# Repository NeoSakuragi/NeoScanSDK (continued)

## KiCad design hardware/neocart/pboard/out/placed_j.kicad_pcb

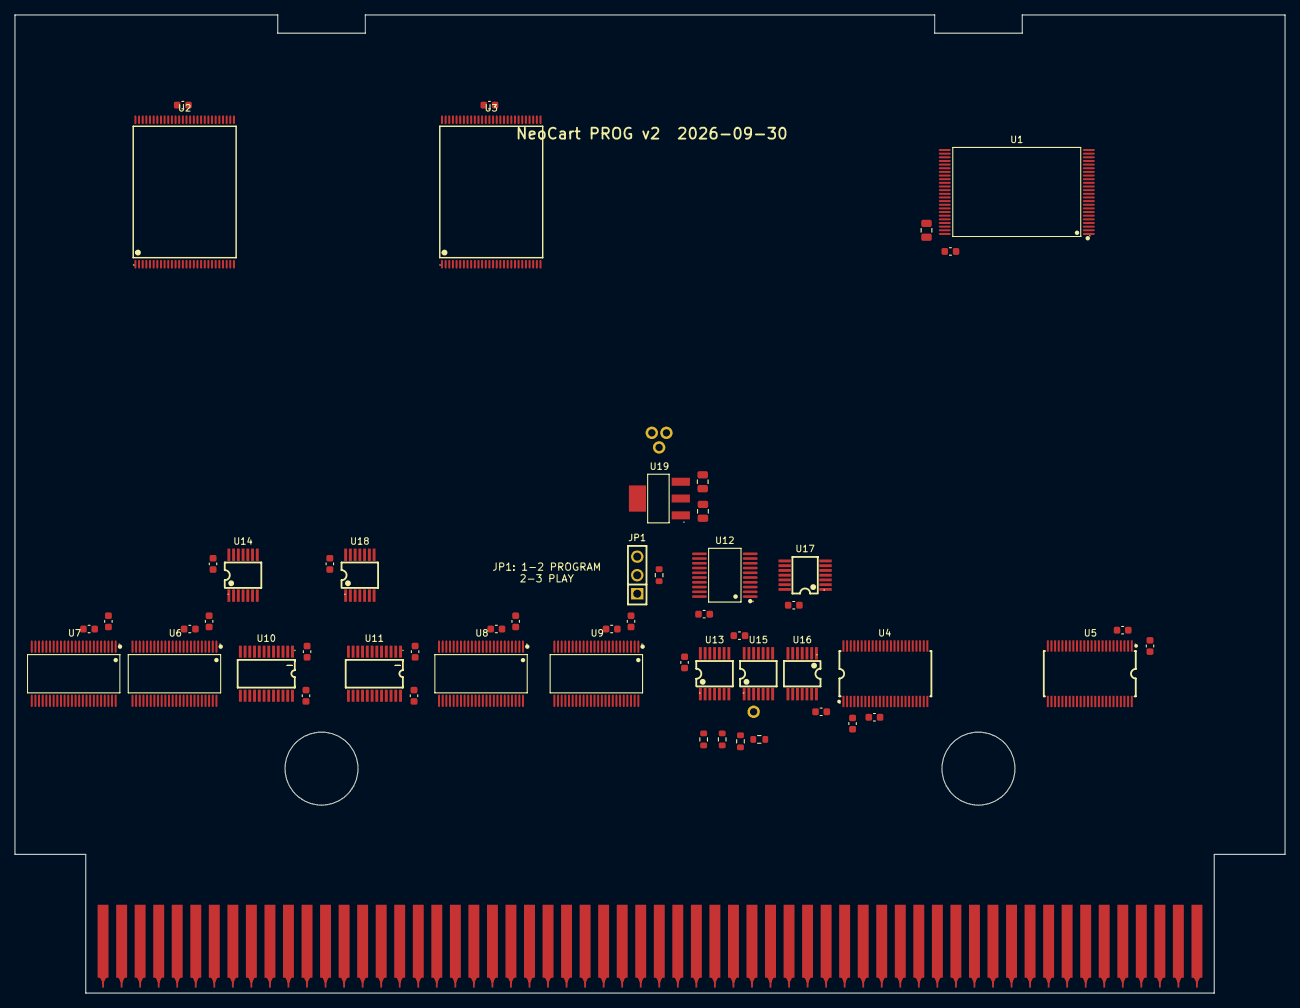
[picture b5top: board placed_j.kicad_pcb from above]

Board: 2 copper layers, 174.0 x 134.0 mm, 60 parts (1 on the bottom side), 202 nets, no tracks yet.

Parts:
C1, C2, C3: 10u; C_0805_2012Metric
C4, C5, C6, C7, C8, C9, C10, C11, C12, C13, C14, C15, C16, C17, C18, C19, C20, C21, C22, C23, C24, C25, C26, C27, C28, C29: 100n; C_0603_1608Metric
J1: NeoGeo MVS Prog B Side Edge; neogeo-mvs-prog-b-side-edge
J2: NeoGeo MVS Prog A Side Edge; neogeo-mvs-prog-a-side-edge
JP1: MODE; HDR-TH_03P-P2.54-V-M
R1, R2, R3, R4, R5: 10k; R_0603_1608Metric
TP1: GND; TP_PTH_1.0
TP2: P3V3; TP_PTH_1.0
TP3: VCC5; TP_PTH_1.0
TP4: nPROG; TP_PTH_1.0
U1: S29GL064N; TSOP-48_L12.0-W18.4-P0.50-LS20.0-BL
U2, U3: S29GL128P; TSOP-56_L18.4-W14.0-P0.50-LS20.0-TL
U4, U5: SN74LVC16245A; TSSOP-48_L12.5-W6.1-P0.50-LS8.1-BL
U6, U7, U8, U9: 74LVC16374A; TSSOP-48_L12.6-W6.2-P0.50-LS8.1-BL
U10, U11: 74LVC8T245; TSSOP-24_L7.8-W4.4-P0.65-LS6.4-BL
U12: SN74AHC273; SSOP-20_L7.5-W5.2-P0.65-LS8.0-BL
U13, U14: SN74LVC08A; TSSOP-14_L5.0-W4.4-P0.65-LS6.4-BL
U15, U16, U17: 74LVC32A; TSSOP-14_L5.0-W4.4-P0.65-LS6.4-BL
U18: SN74LVC04A; TSSOP-14_L5.0-W4.4-P0.65-LS6.4-BL
U19: AMS1117-3.3; SOT-223-3_L6.5-W3.4-P2.30-LS7.0-BR

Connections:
A1: J1.5 (A1), U5.47
A2: J1.6 (A2), U5.46
A3: J1.7 (A3), U5.44
A4: J1.8 (A4), U5.43
A5: J1.9 (A5), U5.41
A6: J1.10 (A6), U5.40
A7: J1.11 (A7), U5.38
A8: J1.12 (A8), U5.37
A9: J1.13 (A9), U5.36
A10: J1.14 (A10), U5.35
A11: J1.15 (A11), U5.33
A12: J1.16 (A12), U5.32
A13: J1.17 (A13), U5.30
A14: J1.18 (A14), U5.29
A15: J1.19 (A15), U5.27
A16: J1.20 (A16), U5.26
A17: J1.21 (A17), U16.12
A18: J1.22 (A18), U17.1
A19: J1.23 (A19), U17.4
BANK0: U12.2, U16.1
BANK1: U12.5, U16.4
BANK2: U12.6, U16.9
D0: J2.5 (D0), U4.23
D1: J2.6 (D1), U4.22
D2: J2.7 (D2), U4.20
D3: J2.8 (D3), U4.19
D4: J2.9 (D4), U4.17
D5: J2.10 (D5), U4.16
D6: J2.11 (D6), U4.14
D7: J2.12 (D7), U4.13
D8: J2.13 (D8), U4.12
D9: J2.14 (D9), U4.11
D10: J2.15 (D10), U4.9
D11: J2.16 (D11), U4.8
D12: J2.17 (D12), U4.6
D13: J2.18 (D13), U4.5
D14: J2.19 (D14), U4.3
D15: J2.20 (D15), U4.2
FA0: U1.25, U5.2
FA1: U1.24, U5.3
FA2: U1.23, U5.5
FA3: U1.22, U5.6
FA4: U1.21, U5.8
FA5: U1.20, U5.9
FA6: U1.19, U5.11
FA7: U1.18, U5.12
FA8: U1.8, U5.13
FA9: U1.7, U5.14
FA10: U1.6, U5.16
FA11: U1.5, U5.17
FA12: U1.4, U5.19
FA13: U1.3, U5.20
FA14: U1.2, U5.22
FA15: U1.1, U5.23
FA16: U1.48, U16.11
FA17: U1.17, U17.3
FA18: U1.16, U17.6
FA19: U1.9, U16.3
FA20: U1.10, U16.6
FA21: U1.13, U16.8
FD0: U1.29, U4.26, U12.3
FD1: U1.31, U4.27, U12.4
FD2: U1.33, U4.29, U12.7
FD3: U1.35, U4.30
FD4: U1.38, U4.32
FD5: U1.40, U4.33
FD6: U1.42, U4.35
FD7: U1.44, U4.36
FD8: U1.30, U4.37
FD9: U1.32, U4.38
FD10: U1.34, U4.40
FD11: U1.36, U4.41
FD12: U1.39, U4.43
FD13: U1.41, U4.44
FD14: U1.43, U4.46
FD15: U1.45, U4.47
GND: C1.2, C2.2, C3.2, C4.2, C5.2, C6.2, C7.2, C8.2, C9.2, C10.2, C11.2, C12.2, C13.2, C14.2, C15.2, C16.2, C17.2, C18.2, C19.2, C20.2, C21.2, C22.2, C23.2, C24.2, C25.2, C26.2, C27.2, C28.2, C29.2, J1.1 (GND), J1.2 (GND), J1.3 (GND), J1.4 (GND), J1.57 (GND), J1.58 (GND), J1.59 (GND), J1.60 (GND), J2.1 (GND), J2.2 (GND), J2.3 (GND), J2.4 (GND), J2.57 (GND), J2.58 (GND), J2.59 (GND), J2.60 (GND), JP1.2, TP1.1, U1.26, U1.27, U1.46, U2.32, U2.33, U2.52, U2.53, U3.32, U3.33, U3.52, U3.53, U4.4, U4.10, U4.15, U4.21, U4.28, U4.34, U4.39, U4.45, U5.4, U5.10, U5.15, U5.21, U5.25, U5.28, U5.34, U5.39, U5.45, U5.48, U6.1, U6.4, U6.10, U6.15, U6.21, U6.24, U6.26, U6.27, U6.28, U6.29, U6.30, U6.32, U6.33, U6.34, U6.39, U6.45, U7.1, U7.4, U7.10, U7.15, U7.21, U7.24, U7.26, U7.27, U7.28, U7.34, U7.39, U7.45, U8.1, U8.4, U8.10, U8.15, U8.21, U8.24, U8.26, U8.27, U8.28, U8.29, U8.30, U8.34, U8.39, U8.45, U9.1, U9.4, U9.10, U9.15, U9.21, U9.24, U9.26, U9.27, U9.28, U9.29, U9.30, U9.34, U9.39, U9.45, U10.11, U10.12, U10.13, U11.11, U11.12, U11.13, U12.8, U12.10, U12.13, U12.14, U12.17, U12.18, U13.7, U14.7, U15.7, U16.7, U16.13, U17.2, U17.5, U17.7, U17.9, U17.10, U17.12, U17.13, U18.5, U18.7, U18.9, U18.11, U18.13, U19.1
P3V3: C2.1, C3.1, C4.1, C5.1, C6.1, C7.1, C8.1, C9.1, C10.1, C11.1, C12.1, C13.1, C14.1, C15.1, C16.1, C17.1, C18.1, C19.1, C20.1, C21.1, C22.1, C23.1, C24.1, C25.1, C26.1, C28.1, R1.2, TP2.1, U1.12, U1.14, U1.37, U1.47, U2.14, U2.16, U2.29, U2.43, U3.14, U3.16, U3.29, U3.43, U4.7, U4.18, U4.31, U4.42, U5.1, U5.7, U5.18, U5.24, U5.31, U5.42, U6.7, U6.18, U6.31, U6.42, U7.7, U7.18, U7.31, U7.42, U8.7, U8.18, U8.31, U8.42, U9.7, U9.18, U9.31, U9.42, U10.1, U11.1, U12.20, U13.14, U14.14, U15.14, U16.14, U17.14, U18.14, U19.2, U19.4
RW: J2.21 (R/W), U4.1, U4.24, U15.12
SDPA8: J2.43 (SDPA8), U8.36, U9.36
SDPA9: J2.44 (SDPA9), U8.35, U9.35
SDPA10: J2.45 (SDPA10), U8.33, U9.33
SDPA11: J2.46 (SDPA11), U8.32, U9.32
SDPAD0: J1.41 (SDPAD0), U8.47, U9.47, U11.21
SDPAD1: J1.42 (SDPAD1), U8.46, U9.46, U11.20
SDPAD2: J1.43 (SDPAD2), U8.44, U9.44, U11.19
SDPAD3: J1.44 (SDPAD3), U8.43, U9.43, U11.18
SDPAD4: J1.45 (SDPAD4), U8.41, U9.41, U11.17
SDPAD5: J1.46 (SDPAD5), U8.40, U9.40, U11.16
SDPAD6: J1.47 (SDPAD6), U8.38, U9.38, U11.15
SDPAD7: J1.48 (SDPAD7), U8.37, U9.37, U11.14
SDPMPX: J2.47 (SDPMPX), U8.25, U8.48, U18.3
SDRA8: J2.49 (SDRA8), U6.36, U7.36
SDRA9: J2.50 (SDRA9), U6.35, U7.35
SDRA20: J2.51 (SDRA20), U7.33
SDRA21: J2.52 (SDRA21), U7.32
SDRA22: J2.53 (SDRA22), U7.30
SDRA23: J2.54 (SDRA23), U7.29
SDRAD0: J1.49 (SDRAD0), U6.47, U7.47, U10.21
SDRAD1: J1.50 (SDRAD1), U6.46, U7.46, U10.20
SDRAD2: J1.51 (SDRAD2), U6.44, U7.44, U10.19
SDRAD3: J1.52 (SDRAD3), U6.43, U7.43, U10.18
SDRAD4: J1.53 (SDRAD4), U6.41, U7.41, U10.17
SDRAD5: J1.54 (SDRAD5), U6.40, U7.40, U10.16
SDRAD6: J1.55 (SDRAD6), U6.38, U7.38, U10.15
SDRAD7: J1.56 (SDRAD7), U6.37, U7.37, U10.14
SDRMPX: J2.55 (SDRMPX), U6.25, U6.48, U18.1
VA_ADR0: U2.51, U6.2
VA_ADR1: U2.31, U6.3
VA_ADR2: U2.26, U6.5
VA_ADR3: U2.25, U6.6
VA_ADR4: U2.24, U6.8
VA_ADR5: U2.23, U6.9
VA_ADR6: U2.22, U6.11
VA_ADR7: U2.21, U6.12
VA_ADR8: U2.20, U6.13
VA_ADR9: U2.10, U6.14
VA_ADR10: U2.9, U7.2
VA_ADR11: U2.8, U7.3
VA_ADR12: U2.7, U7.5
VA_ADR13: U2.6, U7.6
VA_ADR14: U2.5, U7.8
VA_ADR15: U2.4, U7.9
VA_ADR16: U2.3, U7.11
VA_ADR17: U2.54, U7.12
VA_ADR18: U2.19, U7.13
VA_ADR19: U2.18, U7.14
VA_ADR20: U2.11, U7.16
VA_ADR21: U2.12, U7.17
VA_ADR22: U2.15, U7.19
VA_ADR23: U2.2, U7.20
VA_DQ0: U2.35, U10.3
VA_DQ1: U2.37, U10.4
VA_DQ2: U2.39, U10.5
VA_DQ3: U2.41, U10.6
VA_DQ4: U2.44, U10.7
VA_DQ5: U2.46, U10.8
VA_DQ6: U2.48, U10.9
VA_DQ7: U2.50, U10.10
VB_ADR0: U3.51, U8.2
VB_ADR1: U3.31, U8.3
VB_ADR2: U3.26, U8.5
VB_ADR3: U3.25, U8.6
VB_ADR4: U3.24, U8.8
VB_ADR5: U3.23, U8.9
VB_ADR6: U3.22, U8.11
VB_ADR7: U3.21, U8.12
VB_ADR8: U3.20, U8.13
VB_ADR9: U3.10, U8.14
VB_ADR10: U3.9, U8.16
VB_ADR11: U3.8, U8.17
VB_ADR12: U3.7, U9.2
VB_ADR13: U3.6, U9.3
VB_ADR14: U3.5, U9.5
VB_ADR15: U3.4, U9.6
VB_ADR16: U3.3, U9.8
VB_ADR17: U3.54, U9.9
VB_ADR18: U3.19, U9.11
VB_ADR19: U3.18, U9.12
VB_ADR20: U3.11, U9.13
VB_ADR21: U3.12, U9.14
VB_ADR22: U3.15, U9.16
VB_ADR23: U3.2, U9.17
VB_DQ0: U3.35, U11.3
VB_DQ1: U3.37, U11.4
VB_DQ2: U3.39, U11.5
VB_DQ3: U3.41, U11.6
VB_DQ4: U3.44, U11.7
VB_DQ5: U3.46, U11.8
VB_DQ6: U3.48, U11.9
VB_DQ7: U3.50, U11.10
VCC5: C1.1, C27.1, C29.1, J1.29 (VCC), J1.30 (VCC), J1.31 (VCC), J1.32 (VCC), J2.29 (VCC), J2.30 (VCC), J2.31 (VCC), J2.32 (VCC), R2.2, R3.2, R4.2, R5.2, TP3.1, U10.23, U10.24, U11.23, U11.24, U19.3
VDIR: U10.2, U11.2, U15.11
nPDTACK: J1.28 (PDTACK), R5.1
nPMPX: U9.25, U9.48, U18.4
nPORTADRS: J2.33 (PORTADRS), U16.2, U16.5, U16.10
nPORTOE: U13.3, U13.5
nPORTOEL: J2.26 (PORTOEL), U13.1
nPORTOEU: J2.25 (PORTOEU), U13.2
nPORTWEL: J2.28 (PORTWEL), U12.11, U13.10
nPORTWEU: J2.27 (PORTWEU), U15.1
nPROG: JP1.1, R1.1, TP4.1, U15.2, U15.5, U15.10, U15.13
nPWAIT0: J1.26 (PWAIT0), R3.1
nPWAIT1: J1.27 (PWAIT1), R4.1
nP_OE: U1.28, U13.6, U13.9
nP_WE: U1.11, U13.13, U15.3
nRESET: J1.35 (RESET), U12.1
nRMPX: U7.25, U7.48, U18.2
nROMOE: J1.33 (ROMOE), U13.4
nROMOEL: J2.24 (ROMOEL), U15.9
nROMOEU: J2.23 (ROMOEU), U15.4
nROMWAIT: J1.25 (ROMWAIT), R2.1
nSDPOE: J2.48 (SDPOE), U14.4, U14.5
nSDROE: J2.56 (SDROE), U14.1, U14.2
nVA_BUFOE: U10.22, U14.8
nVA_OE: U2.34, U14.3, U14.9
nVA_WE: U2.13, U14.10, U15.6
nVB_BUFOE: U11.22, U14.11
nVB_OE: U3.34, U14.6, U14.12
nVB_WE: U3.13, U14.13, U15.8
nXCVR_EN: U4.25, U4.48, U13.11
nXEN1: U13.8, U13.12

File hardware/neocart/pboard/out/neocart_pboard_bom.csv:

Comment,Designator,Footprint,LCSC Part #
100n,"C23,C5,C17,C15,C16,C26,C19,C22,C27,C8,C14,C21,C18,C28,C6,C4,C12,C9,C25,C7,C11,C20,C10,C24,C13",C0603,C14663
74LVC16245A,"U5,U4",TSSOP-48_L12.5-W6.1-P0.50-LS8.1-BL,C548160
74LVC8T245,"U11,U10",TSSOP-24_L7.8-W4.4-P0.65-LS6.4-BL,C458788
10k,"R3,R1,R5,R2,R4",R0603,C25804
74LVC08A,"U13,U14",TSSOP-14_L5.0-W4.4-P0.65-LS6.4-BL,C6053
74LVC32A,"U17,U16,U15",TSSOP-14_L5.0-W4.4-P0.65-LS6.4-BL,C6087
74LVC16374A,"U9,U8,U7,U6",TSSOP-48_L12.6-W6.2-P0.50-LS8.1-BL,C6074
10u,"C2,C3,C1",C0805,C15850
SN74AHC273,U12,SSOP-20_L7.5-W5.2-P0.65-LS8.0-BL,C2877489
S29GL064N,U1,TSOP-48_L12.0-W18.4-P0.50-LS20.0-BL,C117907
S29GL128P,U2,TSOP-56_L18.4-W14.0-P0.50-LS20.0-TL,C914939
SN74LVC04A,U18,TSSOP-14_L5.0-W4.4-P0.65-LS6.4-BL,C352968
AMS1117-3.3,U19,SOT-223-3_L6.5-W3.4-P2.30-LS7.0-BR,C6186

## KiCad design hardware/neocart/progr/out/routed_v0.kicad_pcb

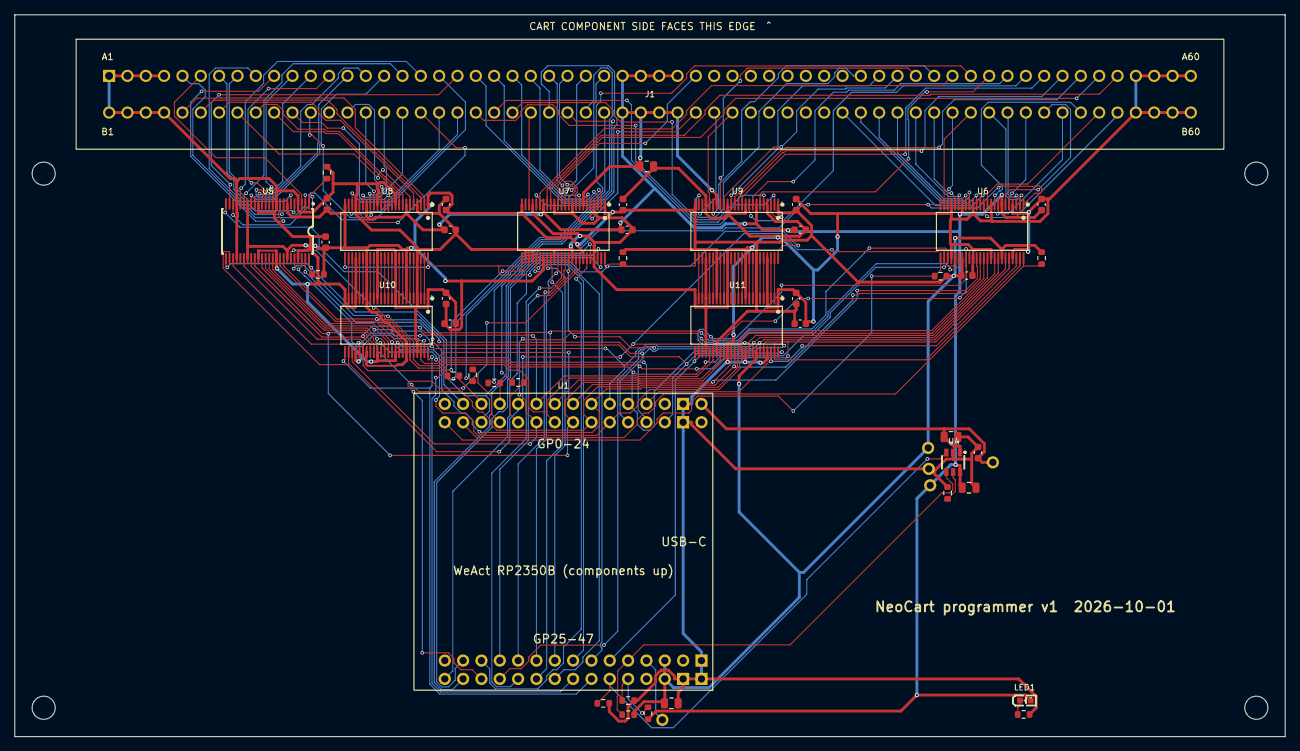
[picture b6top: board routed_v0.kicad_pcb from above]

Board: 2 copper layers, 176.0 x 100.0 mm, 54 parts (0 on the bottom side), 167 nets.

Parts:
C1, C3, C4, C5: 10u; C_0805_2012Metric
C2, C6, C7, C8, C9, C10, C11, C12, C13, C14, C15, C16, C17, C18, C19: 100n; C_0603_1608Metric
J1: MVS slot; MVS_SLOT_EDAC_345-120
LED1: CART; LED-SMD_L1.6-W0.8-R-RD
MH1, MH2, MH3, MH4: M3; MH_M3
R1, R2, R3, R4, R5, R6, R7, R9, R10: 10k; R_0603_1608Metric
R8: 33k; R_0603_1608Metric
R11, R12, R13, R14, R15: 1k; R_0603_1608Metric
TP1: GND; TP_PTH_1.0
TP2: P3V3; TP_PTH_1.0
TP3: VCART; TP_PTH_1.0
TP4: VBUS; TP_PTH_1.0
TP5: GPIO47; TP_PTH_1.0
U1: WeAct RP2350B; WEACT_RP2350B_CORE
U4: TPS2553; SOT-23-6_L2.9-W1.6-P0.95-LS2.8-BR
U5: 74LVC16245A; TSSOP-48_L12.5-W6.1-P0.50-LS8.1-BL
U6, U7, U8, U9: SN74LVC16T245; TSSOP-48_L12.6-W6.2-P0.50-LS8.1-BL
U10, U11: 74LVC16374A; TSSOP-48_L12.6-W6.2-P0.50-LS8.1-BL

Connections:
A1: J1.B5, U8.2
A2: J1.B6, U8.3
A3: J1.B7, U8.5
A4: J1.B8, U8.6
A5: J1.B9, U8.8
A6: J1.B10, U8.9
A7: J1.B11, U8.11
A8: J1.B12, U8.12
A9: J1.B13, U8.13
A10: J1.B14, U8.14
A11: J1.B15, U8.16
A12: J1.B16, U8.17
A13: J1.B17, U8.19
A14: J1.B18, U8.20
A15: J1.B19, U8.22
A16: J1.B20, U8.23
A17: J1.B21, U9.2
A18: J1.B22, U9.3
A19: J1.B23, U9.5
CLK4M: J1.B34, U9.22
CLK68K: J1.B24, U7.22
D0: J1.A5, U5.2
D1: J1.A6, U5.3
D2: J1.A7, U5.5
D3: J1.A8, U5.6
D4: J1.A9, U5.8
D5: J1.A10, U5.9
D6: J1.A11, U5.11
D7: J1.A12, U5.12
D8: J1.A13, U5.13
D9: J1.A14, U5.14
D10: J1.A15, U5.16
D11: J1.A16, U5.17
D12: J1.A17, U5.19
D13: J1.A18, U5.20
D14: J1.A19, U5.22
D15: J1.A20, U5.23
GND: C1.2, C2.2, C3.2, C4.2, C5.2, C6.2, C7.2, C8.2, C9.2, C10.2, C11.2, C12.2, C13.2, C14.2, C15.2, C16.2, C17.2, C18.2, C19.2, J1.A1, J1.A2, J1.A3, J1.A4, J1.A57, J1.A58, J1.A59, J1.A60, J1.B1, J1.B2, J1.B3, J1.B4, J1.B57, J1.B58, J1.B59, J1.B60, R5.2, R6.2, R8.2, R10.2, R15.2, TP1.1, U1.BI2, U1.BO2, U1.TI1, U1.TO1, U1.TO2, U4.2, U5.4, U5.10, U5.15, U5.21, U5.28, U5.34, U5.39, U5.45, U6.4, U6.10, U6.15, U6.21, U6.28, U6.34, U6.39, U6.45, U7.4, U7.10, U7.15, U7.21, U7.26, U7.28, U7.34, U7.39, U7.45, U8.4, U8.10, U8.15, U8.21, U8.28, U8.34, U8.39, U8.45, U9.4, U9.10, U9.15, U9.21, U9.28, U9.34, U9.39, U9.45, U10.1, U10.4, U10.10, U10.15, U10.21, U10.24, U10.28, U10.34, U10.39, U10.45, U11.1, U11.4, U11.10, U11.15, U11.21, U11.24, U11.28, U11.34, U11.39, U11.45
GPIO47: TP5.1, U1.TI4
G_CLK68K: U1.TO8, U7.27
G_RW: U1.TO15, U7.47
G_SDPMPX: U1.TO9, U7.30
G_SDRMPX: U1.TO10, U7.33
G_nAS: U1.TI14, U7.46
G_nPORTADRS: U1.TI10, U7.35
G_nPORTOEL: U1.TO12, U7.38
G_nPORTOEU: U1.TI12, U7.40
G_nPORTWEL: U1.TO11, U7.36
G_nPORTWEU: U1.TI11, U7.37
G_nROMOE: U1.TO14, U7.44
G_nROMOEL: U1.TO13, U7.41
G_nROMOEU: U1.TI13, U7.43
G_nSDPOE: U1.TI8, U7.29
G_nSDROE: U1.TI9, U7.32
ILIM: R8.1, U4.5
LCLK1: U1.TO7, U10.25, U10.48
LCLK2: U1.TI6, U11.25, U11.48
LED1_K: LED1.2, R15.1
L_A1: U8.47, U10.2
L_A2: U8.46, U10.3
L_A3: U8.44, U10.5
L_A4: U8.43, U10.6
L_A5: U8.41, U10.8
L_A6: U8.40, U10.9
L_A7: U8.38, U10.11
L_A8: U8.37, U10.12
L_A9: U8.36, U10.13
L_A10: U8.35, U10.14
L_A11: U8.33, U10.16
L_A12: U8.32, U10.17
L_A13: U8.30, U10.19
L_A14: U8.29, U10.20
L_A15: U8.27, U10.22
L_A16: U8.26, U10.23
L_A17: U9.47, U11.2
L_A18: U9.46, U11.3
L_A19: U9.44, U11.5
L_CLK4M: U9.27, U11.22
L_SDPA8: U9.35, U11.14
L_SDPA9: U9.33, U11.16
L_SDPA10: U9.32, U11.17
L_SDPA11: U9.30, U11.19
L_SDRA8: U9.43, U11.6
L_SDRA9: U9.41, U11.8
L_SDRA20: U9.40, U11.9
L_SDRA21: U9.38, U11.11
L_SDRA22: U9.37, U11.12
L_SDRA23: U9.36, U11.13
L_nRESET: U9.29, U11.20
L_nSLOTCS: U9.26, U11.23
MD0: U1.BI3, U5.47, U6.47, U10.47, U11.47
MD1: U1.BO4, U5.46, U6.46, U10.46, U11.46
MD2: U1.BI4, U5.44, U6.44, U10.44, U11.44
MD3: U1.BO5, U5.43, U6.43, U10.43, U11.43
MD4: U1.BI5, U5.41, U6.41, U10.41, U11.41
MD5: U1.BO6, U5.40, U6.40, U10.40, U11.40
MD6: U1.BI6, U5.38, U6.38, U10.38, U11.38
MD7: U1.BO7, U5.37, U6.37, U10.37, U11.37
MD8: U1.BI7, U5.36, U6.36, U10.36, U11.36
MD9: U1.BO8, U5.35, U6.35, U10.35, U11.35
MD10: U1.BI8, U5.33, U6.33, U10.33, U11.33
MD11: U1.BO9, U5.32, U6.32, U10.32, U11.32
MD12: U1.BI9, U5.30, U6.30, U10.30, U11.30
MD13: U1.BO10, U5.29, U6.29, U10.29, U11.29
MD14: U1.BI10, U5.27, U6.27, U10.27, U11.27
MD15: U1.BO11, U5.26, U6.26, U10.26, U11.26
P3V3: C5.1, C6.1, C7.1, C8.1, C9.1, C10.1, C11.1, C12.1, C14.1, C16.1, C18.1, R1.2, R2.2, R3.2, R4.2, R7.2, TP2.1, U1.TI3, U1.TO3, U5.7, U5.18, U5.31, U5.42, U6.31, U6.42, U7.1, U7.24, U7.31, U7.42, U8.1, U8.24, U8.31, U8.42, U9.1, U9.24, U9.31, U9.42, U10.7, U10.18, U10.31, U10.42, U11.7, U11.18, U11.31, U11.42
RW: J1.A21, U7.2
SDPA8: J1.A43, U9.14
SDPA9: J1.A44, U9.16
SDPA10: J1.A45, U9.17
SDPA11: J1.A46, U9.19
SDPAD0: J1.B41, U6.13
SDPAD1: J1.B42, U6.14
SDPAD2: J1.B43, U6.16
SDPAD3: J1.B44, U6.17
SDPAD4: J1.B45, U6.19
SDPAD5: J1.B46, U6.20
SDPAD6: J1.B47, U6.22
SDPAD7: J1.B48, U6.23
SDPMPX: J1.A47, U7.19
SDRA8: J1.A49, U9.6
SDRA9: J1.A50, U9.8
SDRA20: J1.A51, U9.9
SDRA21: J1.A52, U9.11
SDRA22: J1.A53, U9.12
SDRA23: J1.A54, U9.13
SDRAD0: J1.B49, U6.2
SDRAD1: J1.B50, U6.3
SDRAD2: J1.B51, U6.5
SDRAD3: J1.B52, U6.6
SDRAD4: J1.B53, U6.8
SDRAD5: J1.B54, U6.9
SDRAD6: J1.B55, U6.11
SDRAD7: J1.B56, U6.12
SDRMPX: J1.A55, U7.16
S_nPDTACK: R14.2, U1.BO13
S_nPWAIT0: R12.2, U1.BO12
S_nPWAIT1: R13.2, U1.BI12
S_nROMWAIT: R11.2, U1.BI11
VBUS: C1.1, C2.1, TP4.1, U1.BO1, U4.1
VCART: C3.1, C4.1, C13.1, C15.1, C17.1, C19.1, J1.A29, J1.A30, J1.A31, J1.A32, J1.B29, J1.B30, J1.B31, J1.B32, LED1.1, R9.1, TP3.1, U4.6, U6.7, U6.18, U7.7, U7.18, U8.7, U8.18, U9.7, U9.18
VCART_EN: R6.1, U1.TO6, U4.3
VCART_SENSE: R9.2, R10.1, U1.TO5
XDIR: R5.1, U1.BI13, U5.1, U5.24, U6.1, U6.24
nAS: J1.A22, U7.3
nOE_D: R1.1, U1.BO14, U5.25, U5.48
nOE_OUT: R4.1, U1.TI7, U7.25, U7.48, U8.25, U8.48, U9.25, U9.48
nOE_VA: R2.1, U1.BI14, U6.48
nOE_VB: R3.1, U1.BI15, U6.25
nPDTACK: J1.B28, R14.1
nPORTADRS: J1.A33, U7.14
nPORTOEL: J1.A26, U7.11
nPORTOEU: J1.A25, U7.9
nPORTWEL: J1.A28, U7.13
nPORTWEU: J1.A27, U7.12
nPWAIT0: J1.B26, R12.1
nPWAIT1: J1.B27, R13.1
nRESET: J1.B35, U9.20
nROMOE: J1.B33, U7.5
nROMOEL: J1.A24, U7.8
nROMOEU: J1.A23, U7.6
nROMWAIT: J1.B25, R11.1
nSDPOE: J1.A48, U7.20
nSDROE: J1.A56, U7.17
nSLOTCS: J1.A42, U9.23
nVCART_FAULT: R7.1, U1.TI5, U4.4

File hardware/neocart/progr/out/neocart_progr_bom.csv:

Comment,Designator,Footprint,LCSC Part #
100n,"C12,C6,C11,C9,C18,C8,C2,C7,C19,C15,C10,C17,C16,C14,C13",C0603,C14663
10k,"R1,R2,R4,R9,R5,R6,R7,R10,R3",R0603,C25804
1k,"R15,R12,R14,R11,R13",R0603,C21190
CART,LED1,LED-SMD_L1.6-W0.8-R-RD,C2286
SN74LVC16T245,"U9,U6,U7,U8",TSSOP-48_L12.6-W6.2-P0.50-LS8.1-BL,C148170
TPS2553,U4,SOT-23-6_L2.9-W1.6-P0.95-LS2.8-BR,C55266
10u,"C3,C5,C4,C1",C0805,C15850
74LVC16245A,U5,TSSOP-48_L12.5-W6.1-P0.50-LS8.1-BL,C548160
74LVC16374A,"U10,U11",TSSOP-48_L12.6-W6.2-P0.50-LS8.1-BL,C6074
33k,R8,R0603,C4216

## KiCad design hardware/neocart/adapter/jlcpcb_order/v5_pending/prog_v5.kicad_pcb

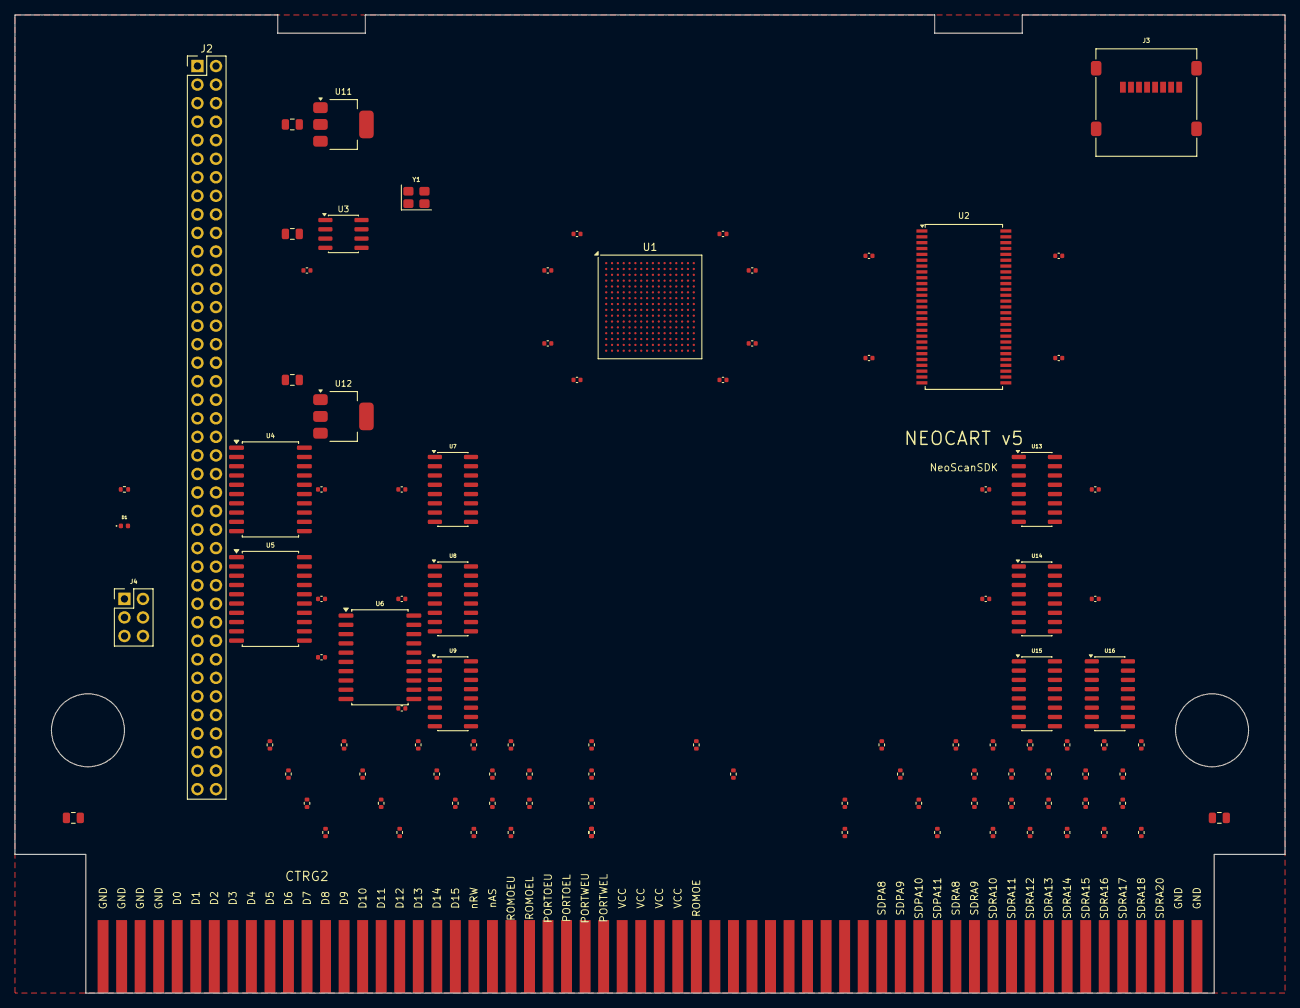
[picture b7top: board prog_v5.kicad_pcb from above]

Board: 4 copper layers, 174.0 x 134.0 mm, 103 parts (0 on the bottom side), 285 nets, no tracks yet.

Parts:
C1, C2, C3, C4, C5, C6, C7, C8, C9, C10, C11, C12, C13, C14, C15, C16, C17, C18, C19, C20, C21, C22, C23: 100nF; C_0402_1005Metric
C24, C25, C26, C27, C28: 10uF; C_0805_2012Metric
CTRG2: MVS_PROG
D1: LED; LED_0402_1005Metric
J2: TO_CHA; PinHeader_2x40_P2.54mm_Vertical
J3: microSD; microSD_HC_Molex_47219-2001
J4: JTAG; PinHeader_2x03_P2.54mm_Vertical
R1, R2, R3, R4, R5, R6, R7, R8, R9, R10, R11, R12, R13, R14, R15, R16, R17, R18, R19, R20, R21, R22, R23, R24, R25, R26, R27, R28, R29, R30, R31, R32, R33, R34, R35, R36, R37, R38, R39, R40, R41, R42, R43, R44, R45, R46, R47, R48, R49, R50, R51, R52, R53: 470R; R_0402_1005Metric
R54: 1K; R_0402_1005Metric
U1: LFE5U-45F; BGA-256_14.0x14.0mm_Layout16x16_P0.8mm_Ball0.45mm_Pad0.32mm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
U2: W9825G6KH; TSOP-II-54_22.2x10.16mm_P0.8mm
U3: W25Q32; SOIC-8_3.9x4.9mm_P1.27mm
U4, U5, U6: 74LVC245; SOIC-20W_7.5x12.8mm_P1.27mm
U7, U8, U9, U13, U14, U15, U16: 74HC165; SOIC-16_3.9x9.9mm_P1.27mm
U11: AMS1117-3.3; SOT-223-3_TabPin2
U12: AMS1117-1.2; SOT-223-3_TabPin2
Y1: 50MHz; Crystal_SMD_3225-4Pin_3.2x2.5mm

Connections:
68KCLK: CTRG2.B24, R25.1
A1: CTRG2.B5, R1.1
A1_R: R1.2, U7.7
A2: CTRG2.B6, R2.1
A2_R: R2.2, U7.6
A3: CTRG2.B7, R3.1
A3_R: R3.2, U7.5
A4: CTRG2.B8, R4.1
A4_R: R4.2, U7.4
A5: CTRG2.B9, R5.1
A5_R: R5.2, U7.3
A6: CTRG2.B10, R6.1
A6_R: R6.2, U7.13
A7: CTRG2.B11, R7.1
A7_R: R7.2, U7.12
A8: CTRG2.B12, R8.1
A8_R: R8.2, U7.11
A9: CTRG2.B13, R9.1
A9_R: R9.2, U8.7
A10: CTRG2.B14, R10.1
A10_R: R10.2, U8.6
A11: CTRG2.B15, R11.1
A11_R: R11.2, U8.5
A12: CTRG2.B16, R12.1
A12_R: R12.2, U8.4
A13: CTRG2.B17, R13.1
A13_R: R13.2, U8.3
A14: CTRG2.B18, R14.1
A14_R: R14.2, U8.13
A15: CTRG2.B19, R15.1
A15_R: R15.2, U8.12
A16: CTRG2.B20, R16.1
A16_R: R16.2, U8.11
A17: CTRG2.B21, R17.1
A17_R: R17.2, U9.7
A18: CTRG2.B22, R18.1
A18_R: R18.2, U9.6
A19: CTRG2.B23, R19.1
A19_R: R19.2, U9.5
BUF_OE: U1.G2, U4.19, U5.19
BUS_DIR: U1.F5, U4.1, U5.1
CHA_CA4: J2.69, U1.K5
CLK8M: J2.67, U1.K3
CLK12M: J2.66, U1.K2
CLK24M: J2.65, U1.K1
CLK_C: J2.58, U1.G1
CLK_P: U1.E4, U7.2, U8.2, U9.2
CLK_S: J2.61, U1.J2
CLK_SD: U1.F3, U13.2, U14.2, U15.2, U16.2
CR0: J2.9, U1.F12
CR1: J2.10, U1.F13
CR2: J2.11, U1.F14
CR3: J2.12, U1.F15
CR4: J2.13, U1.F16
CR5: J2.14, U1.G12
CR6: J2.15, U1.G13
CR7: J2.16, U1.G14
CR8: J2.17, U1.G15
CR9: J2.18, U1.G16
CR10: J2.19, U1.H12
CR11: J2.20, U1.H13
CR12: J2.21, U1.H14
CR13: J2.22, U1.H15
CR14: J2.23, U1.J12
CR15: J2.24, U1.J13
CR16: J2.25, U1.J14
CR17: J2.26, U1.J15
CR18: J2.27, U1.J16
CR19: J2.28, U1.K12
CR20: J2.29, U1.K13
CR21: J2.30, U1.K14
CR22: J2.31, U1.K15
CR23: J2.32, U1.K16
CR24: J2.33, U1.L12
CR25: J2.34, U1.L13
CR26: J2.35, U1.L14
CR27: J2.36, U1.L15
CR28: J2.37, U1.L16
CR29: J2.38, U1.D10
CR30: J2.39, U1.D11
CR31: J2.40, U1.D12
D0: CTRG2.A5, U4.2
D1: CTRG2.A6, U4.3
D2: CTRG2.A7, U4.4
D3: CTRG2.A8, U4.5
D4: CTRG2.A9, U4.6
D5: CTRG2.A10, U4.7
D6: CTRG2.A11, U4.8
D7: CTRG2.A12, U4.9
D8: CTRG2.A13, U5.2
D9: CTRG2.A14, U5.3
D10: CTRG2.A15, U5.4
D11: CTRG2.A16, U5.5
D12: CTRG2.A17, U5.6
D13: CTRG2.A18, U5.7
D14: CTRG2.A19, U5.8
D15: CTRG2.A20, U5.9
FD0: U1.A2, U4.18
FD1: U1.A3, U4.17
FD2: U1.A4, U4.16
FD3: U1.A5, U4.15
FD4: U1.A6, U4.14
FD5: U1.A7, U4.13
FD6: U1.B2, U4.12
FD7: U1.B3, U4.11
FD8: U1.B4, U5.18
FD9: U1.B5, U5.17
FD10: U1.B6, U5.16
FD11: U1.B7, U5.15
FD12: U1.C2, U5.14
FD13: U1.C3, U5.13
FD14: U1.C4, U5.12
FD15: U1.C5, U5.11
FIX0: J2.49, U1.E13
FIX1: J2.50, U1.E14
FIX2: J2.51, U1.E15
FIX3: J2.52, U1.E16
FIX4: J2.53, U1.E6
FIX5: J2.54, U1.E7
FIX6: J2.55, U1.E8
FIX7: J2.56, U1.E9
FLASH_CLK: U1.C1, U3.6
FLASH_CS: U1.B1, U3.1
FLASH_MISO: U1.E1, U3.2
FLASH_MOSI: U1.D1, U3.5
FSD0: U1.C6, U6.2
FSD1: U1.C7, U6.3
FSD2: U1.D3, U6.4
FSD3: U1.D4, U6.5
FSD4: U1.D5, U6.6
FSD5: U1.D6, U6.7
FSD6: U1.D7, U6.8
FSD7: U1.E2, U6.9
GND: C1.2, C2.2, C3.2, C4.2, C5.2, C6.2, C7.2, C8.2, C9.2, C10.2, C11.2, C12.2, C13.2, C14.2, C15.2, C16.2, C17.2, C18.2, C19.2, C20.2, C21.2, C22.2, C23.2, C24.2, C25.2, C26.2, C27.2, C28.2, CTRG2.A1, CTRG2.A2, CTRG2.A3, CTRG2.A4, CTRG2.A59, CTRG2.A60, CTRG2.B1, CTRG2.B2, CTRG2.B3, CTRG2.B4, CTRG2.B26, CTRG2.B27, CTRG2.B59, CTRG2.B60, D1.2, J2.5, J2.6, J2.7, J2.8, J2.74, J2.75, J2.76, J2.77, J2.78, J2.79, J2.80, J3.3, J3.6, J3.9, J4.6, U2.3, U2.6, U2.9, U2.12, U2.39, U2.43, U2.46, U2.49, U2.52, U3.4, U4.10, U5.10, U6.10, U7.8, U7.10, U7.14, U8.8, U8.14, U9.8, U9.14, U11.1, U12.1, U13.8, U13.10, U13.14, U14.8, U14.14, U15.8, U15.14, U16.3, U16.4, U16.8, U16.11, U16.12, U16.13, U16.14, Y1.3
JTAG_TCK: J4.3, U1.M1
JTAG_TDI: J4.5, U1.M2
JTAG_TDO: J4.4, U1.M3
JTAG_TMS: J4.2, U1.L1
LED1: D1.1, R54.1, U1.M4
LOAD_C: J2.59, U1.H5
LOAD_P: U1.E5, U7.1, U8.1, U9.1
LOAD_S: J2.62, U1.J3
LOAD_SD: U1.F4, U13.1, U14.1, U15.1, U16.1
PCK1B: J2.63, U1.J4
PCK2B: J2.64, U1.J5
RESET: CTRG2.B35, R26.1
ROMOE: CTRG2.A33, R24.1
ROMOEL: CTRG2.A24, R23.1
ROMOEL_R: R23.2, U9.12
ROMOEU: CTRG2.A23, R22.1
ROMOEU_R: R22.2, U9.13
ROMOE_R: R24.2, U9.11
SDD0: J2.41, U1.D13
SDD1: J2.42, U1.D14
SDD2: J2.43, U1.D16
SDD3: J2.44, U1.D8
SDD4: J2.45, U1.D9
SDD5: J2.46, U1.E10
SDD6: J2.47, U1.E11
SDD7: J2.48, U1.E12
SDMRD: CTRG2.B58, R52.1
SDMRD_CHA: J2.71, U1.L3
SDMRD_R: R52.2, U16.6
SDPA8: CTRG2.A43, R48.1
SDPA8_R: R48.2, U15.13
SDPA9: CTRG2.A44, R49.1
SDPA9_R: R49.2, U15.12
SDPA10: CTRG2.A45, R50.1
SDPA10_R: R50.2, U15.11
SDPA11: CTRG2.A46, R51.1
SDPA11_R: R51.2, U16.7
SDPAD0: CTRG2.B40, U6.18
SDPAD1: CTRG2.B41, U6.17
SDPAD2: CTRG2.B42, U6.16
SDPAD3: CTRG2.B43, U6.15
SDPAD4: CTRG2.B44, U6.14
SDPAD5: CTRG2.B45, U6.13
SDPAD6: CTRG2.B46, U6.12
SDPAD7: CTRG2.B47, U6.11
SDRA0: CTRG2.B48, R27.1
SDRA0_R: R27.2, U13.7
SDRA1: CTRG2.B49, R28.1
SDRA1_R: R28.2, U13.6
SDRA2: CTRG2.B50, R29.1
SDRA2_R: R29.2, U13.5
SDRA3: CTRG2.B51, R30.1
SDRA3_R: R30.2, U13.4
SDRA4: CTRG2.B52, R31.1
SDRA4_R: R31.2, U13.3
SDRA5: CTRG2.B53, R32.1
SDRA5_R: R32.2, U13.13
SDRA6: CTRG2.B54, R33.1
SDRA6_R: R33.2, U13.12
SDRA7: CTRG2.B55, R34.1
SDRA7_R: R34.2, U13.11
SDRA8: CTRG2.A47, R35.1
SDRA8_R: R35.2, U14.7
SDRA9: CTRG2.A48, R36.1
SDRA9_R: R36.2, U14.6
SDRA10: CTRG2.A49, R37.1
SDRA10_R: R37.2, U14.5
SDRA11: CTRG2.A50, R38.1
SDRA11_R: R38.2, U14.4
SDRA12: CTRG2.A51, R39.1
SDRA12_R: R39.2, U14.3
SDRA13: CTRG2.A52, R40.1
SDRA13_R: R40.2, U14.13
SDRA14: CTRG2.A53, R41.1
SDRA14_R: R41.2, U14.12
SDRA15: CTRG2.A54, R42.1
SDRA15_R: R42.2, U14.11
SDRA16: CTRG2.A55, R43.1
SDRA16_R: R43.2, U15.7
SDRA17: CTRG2.A56, R44.1
SDRA17_R: R44.2, U15.6
SDRA18: CTRG2.A57, R45.1
SDRA18_R: R45.2, U15.5
SDRA19: CTRG2.B57, R46.1
SDRA19_R: R46.2, U15.4
SDRA20: CTRG2.A58, R47.1
SDRA20_R: R47.2, U15.3
SDRAM_A0: U1.N7, U2.23
SDRAM_A1: U1.N8, U2.24
SDRAM_A2: U1.P11, U2.25
SDRAM_A3: U1.P12, U2.26
SDRAM_A4: U1.P13, U2.29
SDRAM_A5: U1.P14, U2.30
SDRAM_A6: U1.P15, U2.31
SDRAM_A7: U1.P16, U2.32
SDRAM_A8: U1.P6, U2.33
SDRAM_A9: U1.P7, U2.34
SDRAM_A10: U1.P8, U2.22
SDRAM_A11: U1.R12, U2.35
SDRAM_A12: U1.R13, U2.36
SDRAM_BA0: U1.R14, U2.20
SDRAM_BA1: U1.R15, U2.21
SDRAM_CAS: U1.T13, U2.17
SDRAM_CKE: U1.R6, U2.37
SDRAM_CLK: U1.R16, U2.38
SDRAM_CS: U1.R7, U2.19
SDRAM_D0: U1.M11, U2.2
SDRAM_D1: U1.M12, U2.4
SDRAM_D2: U1.M13, U2.5
SDRAM_D3: U1.M14, U2.7
SDRAM_D4: U1.M15, U2.8
SDRAM_D5: U1.M16, U2.10
SDRAM_D6: U1.M6, U2.11
SDRAM_D7: U1.M7, U2.13
SDRAM_D8: U1.M8, U2.42
SDRAM_D9: U1.M9, U2.44
SDRAM_D10: U1.N11, U2.45
SDRAM_D11: U1.N12, U2.47
SDRAM_D12: U1.N13, U2.48
SDRAM_D13: U1.N14, U2.50
SDRAM_D14: U1.N16, U2.51
SDRAM_D15: U1.N6, U2.53
SDRAM_DQM: U1.T15, U2.15
SDRAM_RAS: U1.R8, U2.18
SDRAM_WE: U1.T14, U2.16
SDROE: CTRG2.B56, R53.1
SDROE_R: R53.2, U16.5
SDROM: J2.72, U1.L4
SD_BUF_OE: U1.G3, U6.19
SD_CLK: J3.5, U1.B12
SD_CS: J3.1, U1.B11
SD_MISO: J3.7, U1.B14
SD_MOSI: J3.2, U1.B13
SER_C: J2.57, U1.F1
SER_P: U1.E3, U9.9
SER_S: J2.60, U1.J1
SER_SD: U1.F2, U16.9
SIG_2H1: J2.68, U1.K4
SR1_OUT: U7.9, U8.10
SR2_OUT: U8.9, U9.10
SSR1_OUT: U13.9, U14.10
SSR2_OUT: U14.9, U15.10
SSR3_OUT: U15.9, U16.10
SYSTEMB: J2.70, U1.L2
VCC_1V1: C1.1, C2.1, C3.1, C4.1, C27.1, U12.2
VCC_3V3: C5.1, C6.1, C7.1, C8.1, C9.1, C10.1, C11.1, C12.1, C13.1, C25.1, C26.1, J2.1, J2.2, J3.4, J4.1, R54.2, U2.1, U2.14, U2.27, U2.28, U2.40, U2.41, U2.54, U3.3, U3.7, U3.8, U11.2, U12.3
VCC_5V: C14.1, C15.1, C16.1, C17.1, C18.1, C19.1, C20.1, C21.1, C22.1, C23.1, C24.1, C28.1, CTRG2.A29, CTRG2.A30, CTRG2.A31, CTRG2.A32, CTRG2.B29, CTRG2.B30, CTRG2.B31, CTRG2.B32, J2.3, J2.4, U4.20, U5.20, U6.1, U6.20, U7.16, U8.16, U9.16, U11.3, U13.16, U14.16, U15.16, U16.16
nAS: CTRG2.A22, R21.1
nAS_R: R21.2, U9.3
nRW: CTRG2.A21, R20.1
nRW_R: R20.2, U9.4

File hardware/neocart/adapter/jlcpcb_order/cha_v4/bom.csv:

Comment,Designator,Footprint,LCSC Part #
2x40 female socket 2.54mm 8.5mm,J2,THT,C5224034
470Ω 0402 1%,"R1,R2,R3,R4,R5,R6,R7,R8,R9,R10,R11,R12,R13,R14,R15,R16,R17,R18,R19,R20,R21,R22,R23,R24,R25,R26,R27,R28,R29,R30,R31,R32,R33,R34,R35,R36,R37,R38,R39,R40",0402,C25117
100nF 0402 16V X7R,"C1,C2,C3,C4,C5",0402,C60474
74HC165D SOIC-16,"U1,U2,U3,U4,U5",SOIC-16,C5613
10µF 0805 25V X5R,C6,0805,C15850

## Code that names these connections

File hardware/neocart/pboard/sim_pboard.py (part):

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            for n in dq: self.out(ref, n, Z)

# ---------------------------------------------------------------------------------------------------------------
STROBES_HIGH = dict(nROMOE=1, nROMOEU=1, nROMOEL=1, nPORTOEL=1, nPORTOEU=1, nPORTWEL=1, nPORTWEU=1, nPORTADRS=1,
                    nSDROE=1, nSDPOE=1, nRESET=1, RW=1, nAS=1, nSLOTCS=1, SDRMPX=0, SDPMPX=0, CLK68K=0, CLK4M=0)
def fresh(prog=False):
    s = Sim()
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
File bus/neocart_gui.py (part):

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            romoe = not (self.raw[3] & 0x01)
            pdtack = not (self.raw[6] & 0x01)
            if romoe or pdtack:
                self.rom_labels["P-ROM"].config(text=f"P-ROM  ADDR 0x{paddr:06X}  DATA 0x{pdata:04X}  /OE {'*' if romoe else '-'}  /DTACK {'*' if pdtack else '-'}")
            else:
                self.rom_labels["P-ROM"].config(text=f"P-ROM  idle")

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            pck1b = not (self.raw[68] & 0x01)
            cdtack = not (self.raw[73] & 0x01)
            if pck1b or cdtack:
                self.rom_labels["C-ROM"].config(text=f"C-ROM  ADDR 0x{caddr:07X}  DATA 0x{cdata:04X}  /PCK1B {'*' if pck1b else '-'}  /DTACK {'*' if cdtack else '-'}")
            else:
                self.rom_labels["C-ROM"].config(text=f"C-ROM  idle")

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            sromoe = not (self.raw[131] & 0x01)
            sdtack = not (self.raw[133] & 0x01)
            if sromoe or sdtack:
                self.rom_labels["S-ROM"].config(text=f"S-ROM  ADDR 0x{saddr:05X}  DATA 0x{sdata:02X}  /SDMRD {'*' if sromoe else '-'}  /DTACK {'*' if sdtack else '-'}")
            else:
                self.rom_labels["S-ROM"].config(text=f"S-ROM  idle")

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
